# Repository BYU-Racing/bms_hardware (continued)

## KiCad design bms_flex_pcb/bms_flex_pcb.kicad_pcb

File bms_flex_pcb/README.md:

# BMS Flex PCBs (FPCs) V1 Files

This was originally intended to be used as the connection from the current collector plates on the modules to the
BMS Cell Monitor PCB V1.01. (the FSAE rules calls this connection the "Voltage sense leads")

The idea to use the FPCs was scrapped for the 2027 season in late October of 2026 due to team integration timeline constraints. We defaulted back to using the long leads off the current collector plates.
This is still a totally viable and incredibly sleek solution for future years (many other FSAE teams use this and EV companies are beginning to move towards a solution similar to this)

The main intent behind using these was as follows:
- instead of using very long tabs on the current collector plates we can solder these very close to the cell stack,
eliminating a lot of risk while manufacturing (because with the long collector plate tabs we have a risk of shorting those tabs to neighboring cells)
- We can have the thermistors soldered directly to the FPC and thus have a closer and better thermal connection to the cells
- Another ease of manufacturing is that we can just lay this across the cells and then solder it and its done.

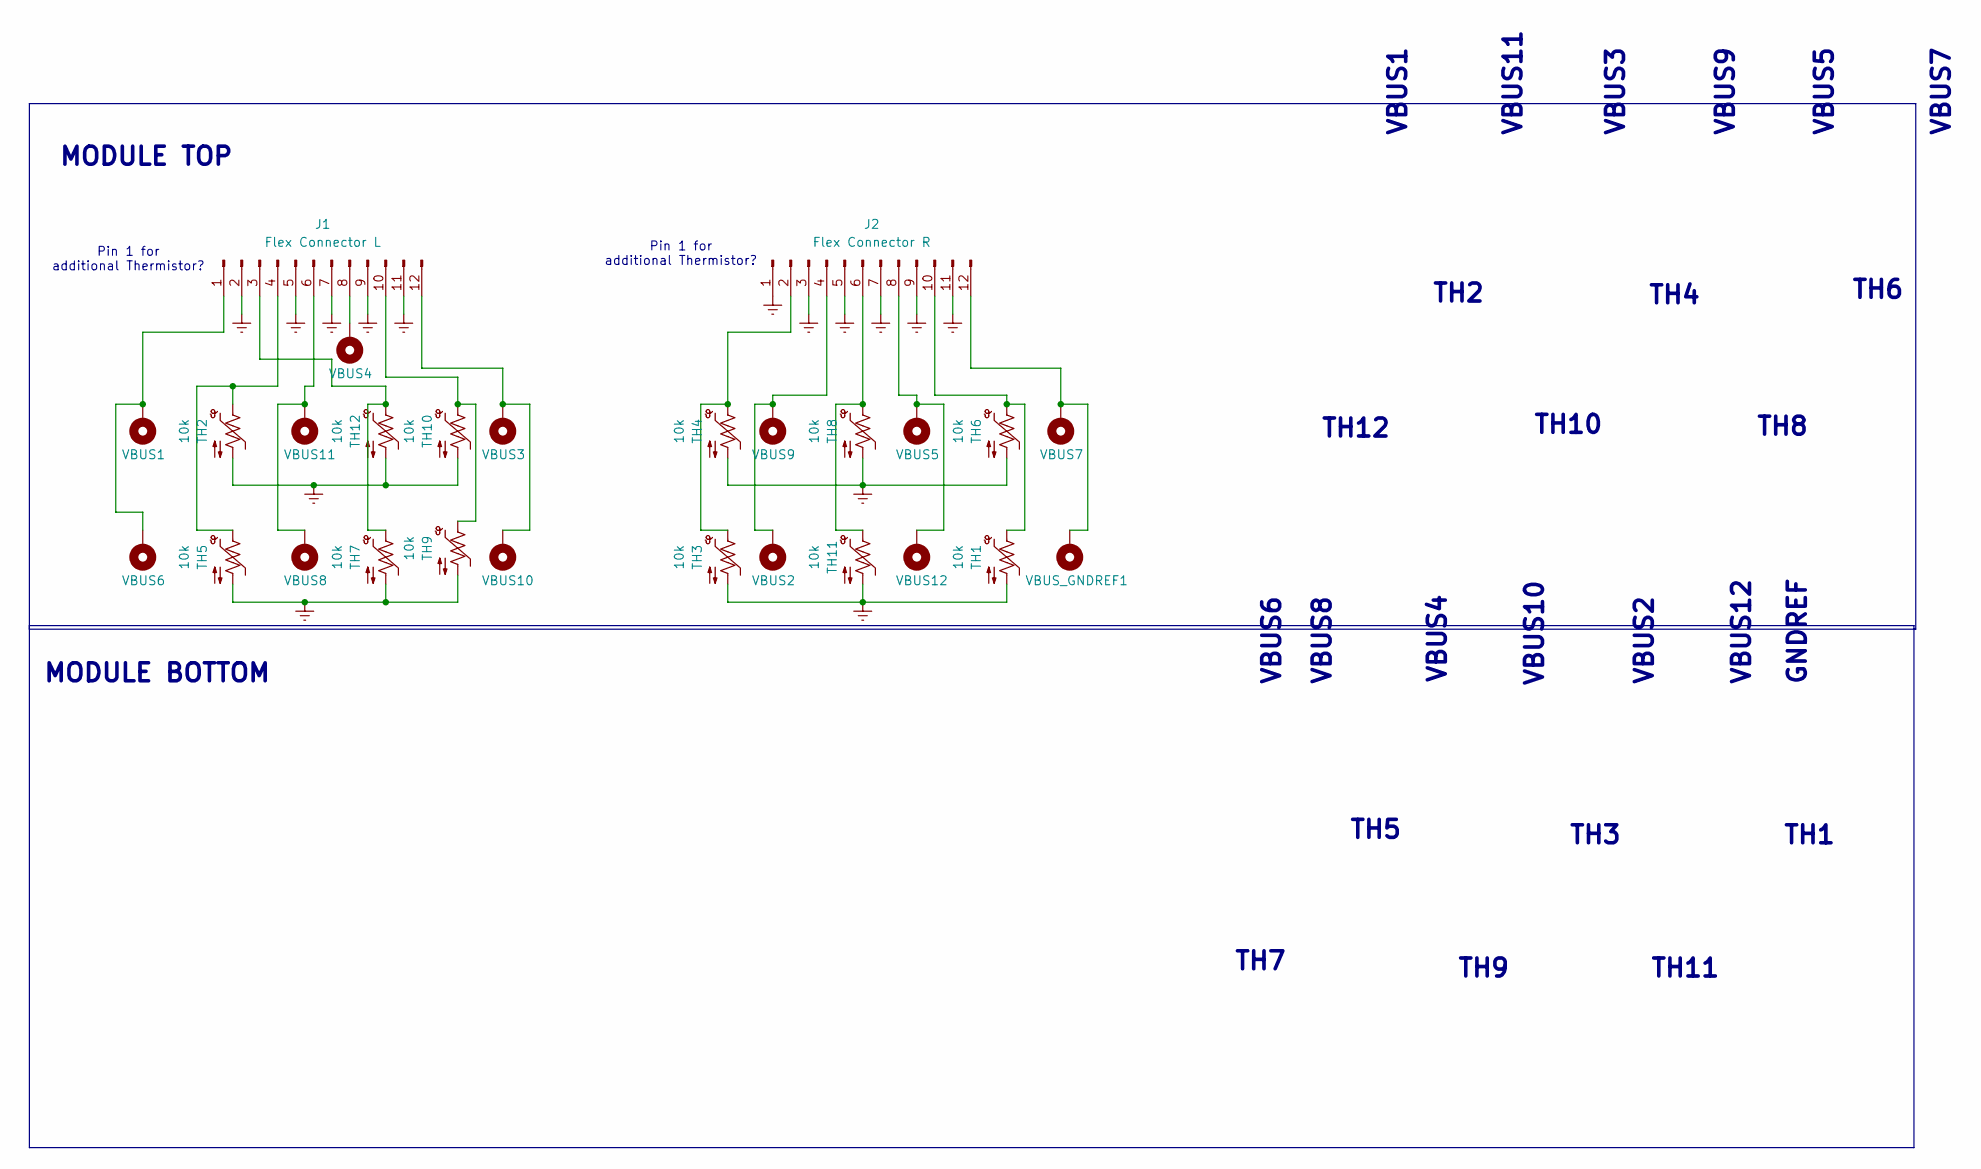
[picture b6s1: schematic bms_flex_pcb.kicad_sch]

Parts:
J1: Flex Connector L; Molex_2190190120_FPC_Board_Connect
J2: Flex Connector R; Molex_2190190120_FPC_Board_Connect
TH1, TH2, TH3, TH4, TH5, TH6, TH7, TH8, TH9, TH10, TH11, TH12: 10k; R_0603_1608Metric_Pad0.98x0.95mm_HandSolder
VBUS1, VBUS2, VBUS3, VBUS4, VBUS5, VBUS6, VBUS7, VBUS8, VBUS9, VBUS10, VBUS11, VBUS12: MountingHole_Pad; 2026_BMS_Voltage_Tap
VBUS_GNDREF1: MountingHole_Pad; 2026_BMS_Voltage_Tap

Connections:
GNDREF: J1.2, J1.5, J1.7, J1.9, J1.11, J2.1, J2.3, J2.5, J2.7, J2.9, J2.11, TH1.2, TH2.2, TH3.2, TH4.2, TH5.2, TH6.2, TH7.2, TH8.2, TH9.2, TH10.2, TH11.2, TH12.2
unnamed: J1.1, VBUS1.1 (1_1), VBUS6.1 (1_1)
unnamed: J1.3, TH7.1, TH12.1
unnamed: J1.4, TH2.1, TH5.1
unnamed: J1.6, VBUS8.1 (1_1), VBUS11.1 (1_1)
unnamed: J1.8, VBUS4.1 (1_1)
unnamed: J1.10, TH9.1, TH10.1
unnamed: J1.12, VBUS3.1 (1_1), VBUS10.1 (1_1)
unnamed: J2.2, TH3.1, TH4.1
unnamed: J2.4, VBUS2.1 (1_1), VBUS9.1 (1_1)
unnamed: J2.6, TH8.1, TH11.1
unnamed: J2.8, VBUS5.1 (1_1), VBUS12.1 (1_1)
unnamed: J2.10, TH1.1, TH6.1
unnamed 13: J2.12, VBUS7.1 (1_1), VBUS_GNDREF1.1; also elsewhere on the board

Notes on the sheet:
GNDREF
TH12
TH7
TH10
MODULE BOTTOM
TH2
VBUS3
VBUS12
VBUS10
TH6
MODULE TOP
Pin 1 for additional Thermistor?
VBUS5
VBUS11
VBUS9
TH8
TH5
TH4
VBUS7
VBUS1
VBUS8
VBUS6
TH3
TH11
VBUS4
TH1
VBUS2
TH9

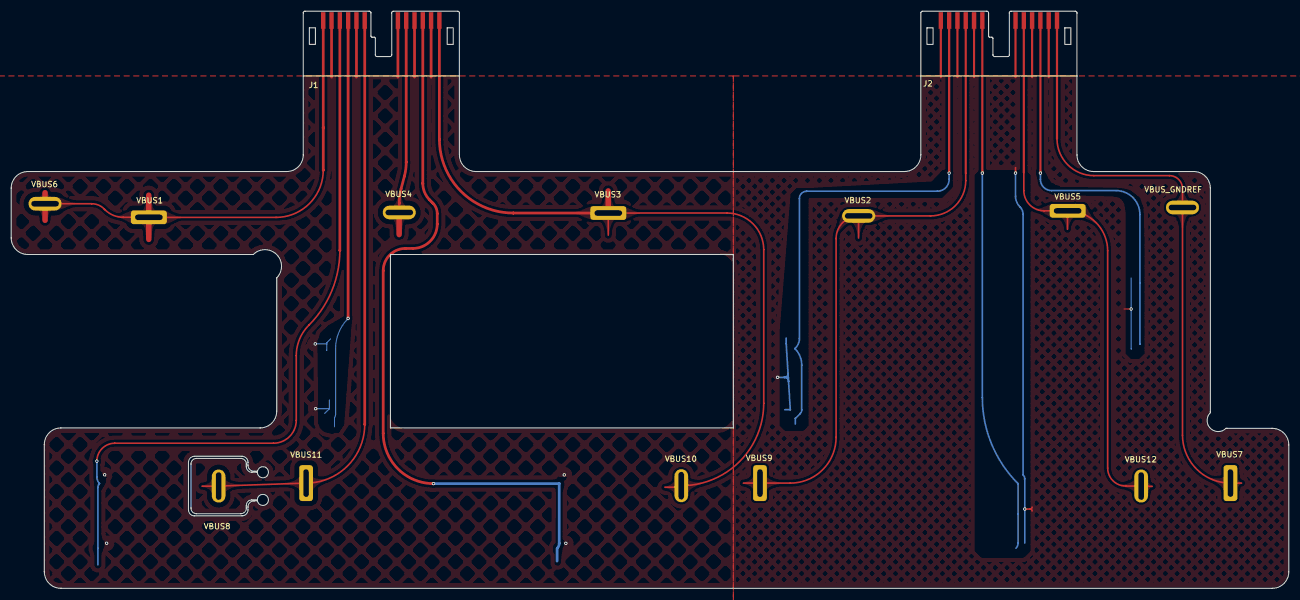
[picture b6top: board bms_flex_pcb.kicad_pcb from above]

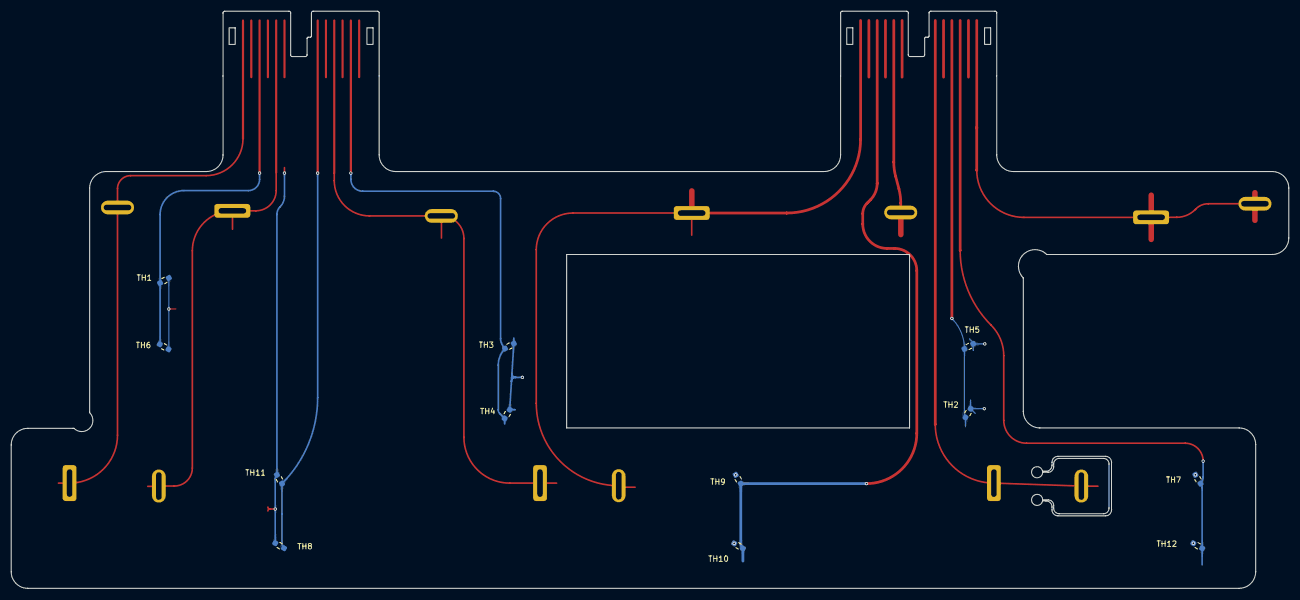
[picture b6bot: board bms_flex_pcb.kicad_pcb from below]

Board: 2 copper layers, 231.0 x 104.3 mm, 27 parts (12 on the bottom side), 14 nets.

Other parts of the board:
VBUS_GNDREF: MountingHole_Pad; 2026_BMS_Voltage_Tap

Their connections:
unnamed 13: VBUS_GNDREF.1 (1_1); also elsewhere on the board

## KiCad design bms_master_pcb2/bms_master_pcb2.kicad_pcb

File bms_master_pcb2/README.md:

## BMS Control Unit V1.01 KiCad Files

These PCB files are for the first version for the BMS Control Unit V1.01 (previously known as the BMS Master V1.01)

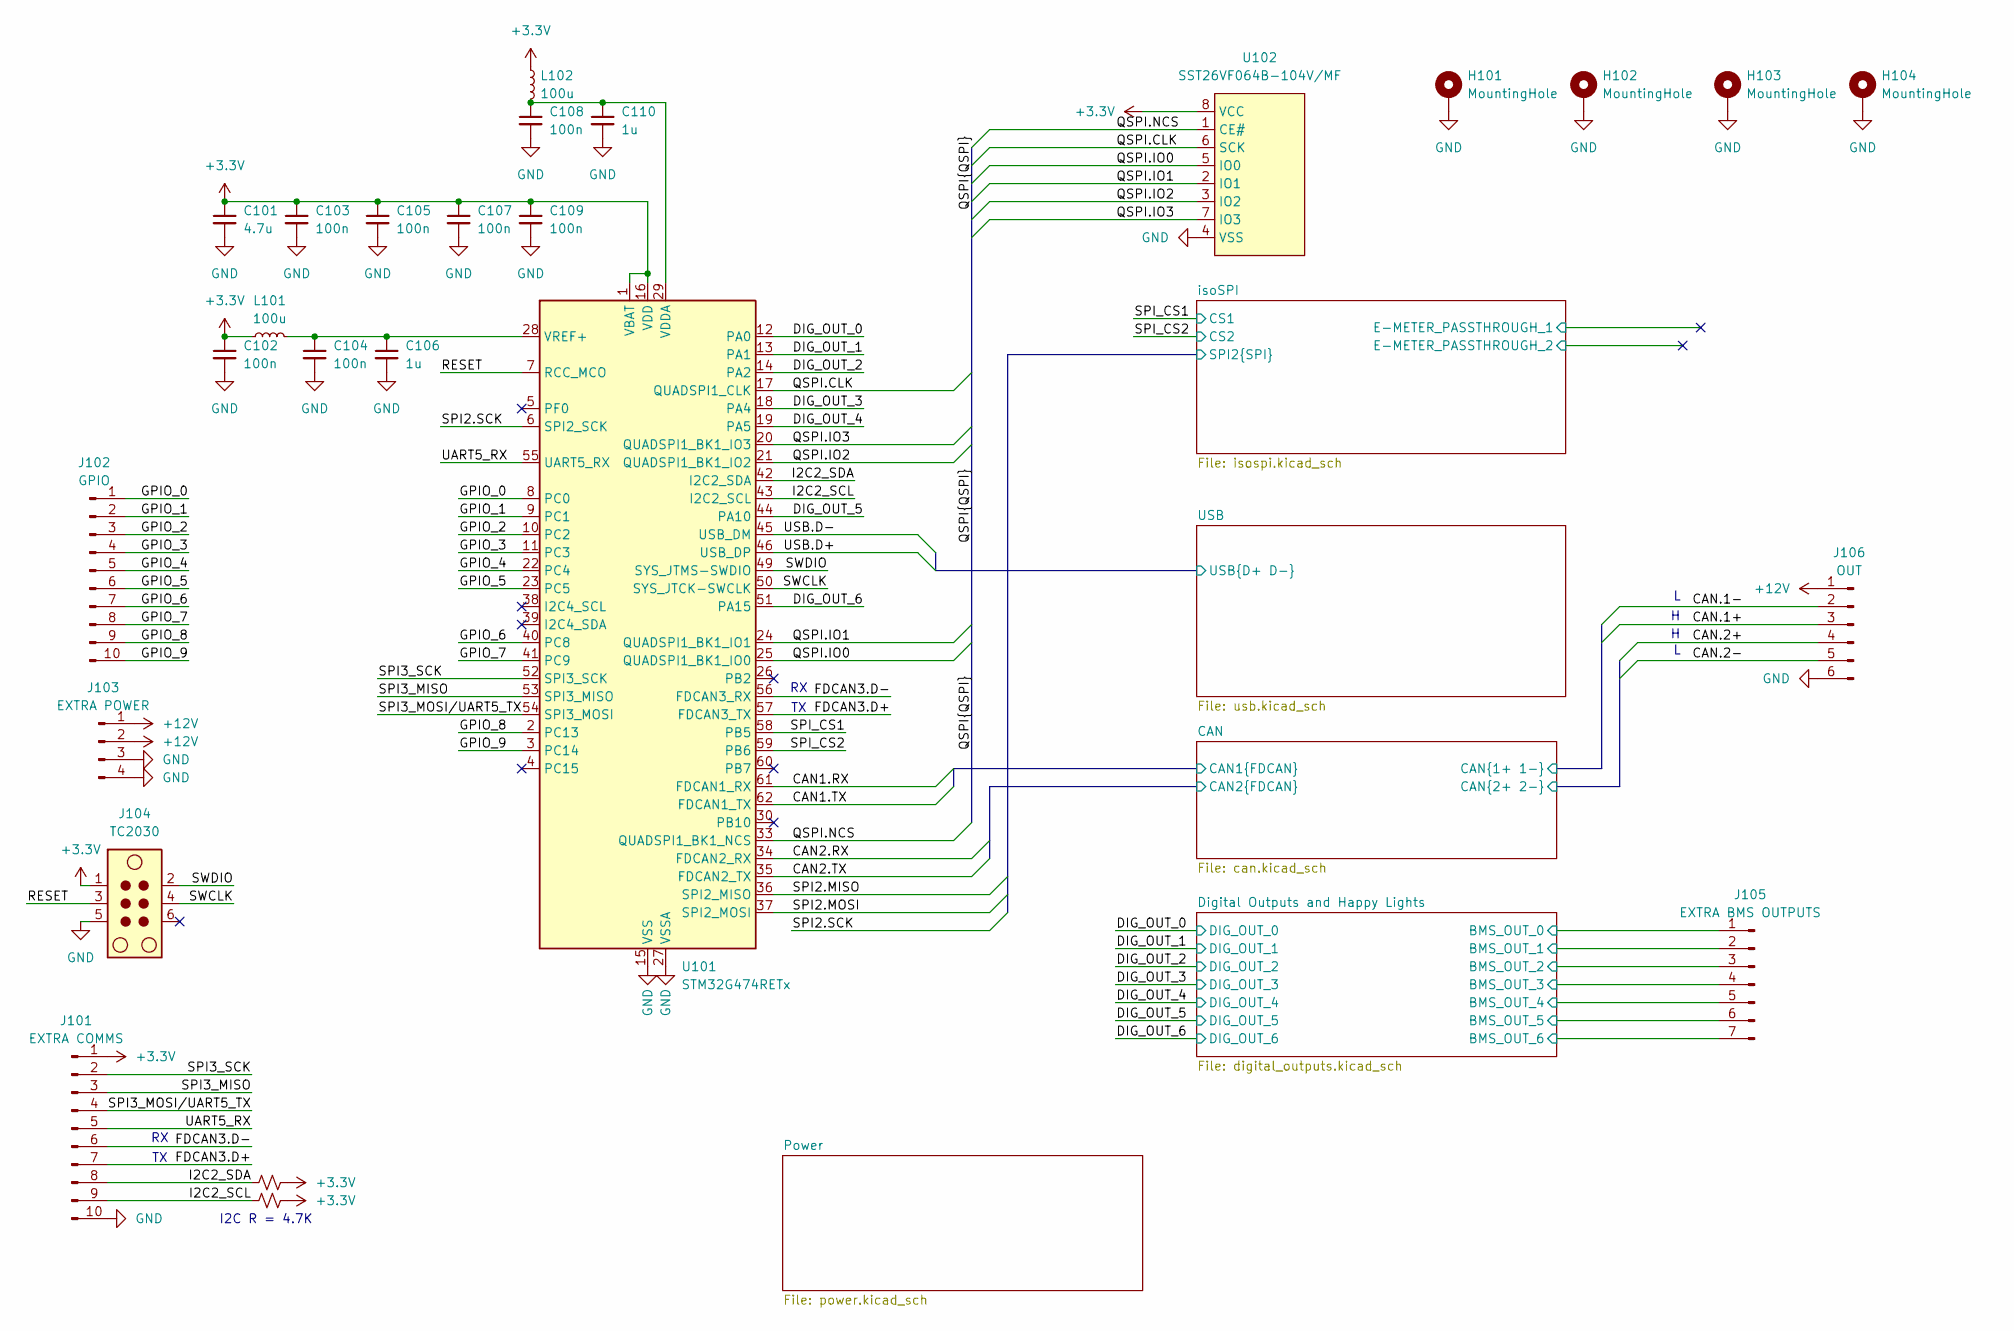
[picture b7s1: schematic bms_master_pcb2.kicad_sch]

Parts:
C101: 4.7u; C_0805_2012Metric_Pad1.18x1.45mm_HandSolder
C102, C103, C104, C105, C107, C108, C109: 100n; C_0603_1608Metric_Pad1.08x0.95mm_HandSolder
C106, C110: 1u; C_0805_2012Metric_Pad1.18x1.45mm_HandSolder
H101, H102, H103, H104: MountingHole; MountingHole_3.2mm_M3_Pad
J101: EXTRA COMMS; PinHeader_1x10_P2.54mm_Vertical
J102: GPIO; PinHeader_1x10_P2.54mm_Vertical
J103: EXTRA POWER; PinHeader_1x04_P2.54mm_Vertical
J104: TC2030; Tag-Connect_TC2030-IDC-NL_2x03_P1.27mm_Vertical
J105: EXTRA BMS OUTPUTS; PinHeader_1x07_P2.54mm_Vertical
J106: OUT; PinHeader_1x06_P2.54mm_Vertical
L101, L102: 100u; WE-HEPC_6030
R101, R102: 4.7K; R_0603_1608Metric_Pad0.98x0.95mm_HandSolder
U101: STM32G474RETx; LQFP-64_10x10mm_P0.5mm
U102: SST26VF064B-104V/MF; WDFN-8-1EP_6x5mm_P1.27mm_EP3.4x4mm

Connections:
+3.3V: C101.1, C102.1, C103.1, C105.1, C107.1, C109.1, J101.1, J104.1, L101.1, L102.1, R101.2, R102.2, U101.1 (VBAT), U101.16 (VDD), U101.32 (VDD), U101.48 (VDD), U101.64 (VDD), U102.8 (VCC); also elsewhere on the board
/CAN/CAN1.RX: U101.61 (FDCAN1_RX); also elsewhere on the board
/CAN/CAN1.TX: U101.62 (FDCAN1_TX); also elsewhere on the board
/CAN/CAN2.RX: U101.34 (FDCAN2_RX); also elsewhere on the board
/CAN/CAN2.TX: U101.35 (FDCAN2_TX); also elsewhere on the board
/CAN/CAN.1+: J106.3; also elsewhere on the board
/CAN/CAN.1-: J106.2; also elsewhere on the board
/CAN/CAN.2+: J106.4; also elsewhere on the board
/CAN/CAN.2-: J106.5; also elsewhere on the board
/DIG_OUT_0: U101.12 (PA0); also elsewhere on the board
/DIG_OUT_1: U101.13 (PA1); also elsewhere on the board
/DIG_OUT_2: U101.14 (PA2); also elsewhere on the board
/DIG_OUT_3: U101.18 (PA4); also elsewhere on the board
/DIG_OUT_4: U101.19 (PA5); also elsewhere on the board
/DIG_OUT_5: U101.44 (PA10); also elsewhere on the board
/DIG_OUT_6: U101.51 (PA15); also elsewhere on the board
/Digital Outputs and Happy Lights/BMS_OUT_0: J105.1; also elsewhere on the board
/Digital Outputs and Happy Lights/BMS_OUT_1: J105.2; also elsewhere on the board
/Digital Outputs and Happy Lights/BMS_OUT_2: J105.3; also elsewhere on the board
/Digital Outputs and Happy Lights/BMS_OUT_3: J105.4; also elsewhere on the board
/Digital Outputs and Happy Lights/BMS_OUT_4: J105.5; also elsewhere on the board
/Digital Outputs and Happy Lights/BMS_OUT_5: J105.6; also elsewhere on the board
/Digital Outputs and Happy Lights/BMS_OUT_6: J105.7; also elsewhere on the board
/FDCAN3.D+: J101.7, U101.57 (FDCAN3_TX)
/FDCAN3.D-: J101.6, U101.56 (FDCAN3_RX)
/GPIO_0: J102.1, U101.8 (PC0)
/GPIO_1: J102.2, U101.9 (PC1)
/GPIO_2: J102.3, U101.10 (PC2)
/GPIO_3: J102.4, U101.11 (PC3)
/GPIO_4: J102.5, U101.22 (PC4)
/GPIO_5: J102.6, U101.23 (PC5)
/GPIO_6: J102.7, U101.40 (PC8)
/GPIO_7: J102.8, U101.41 (PC9)
/GPIO_8: J102.9, U101.2 (PC13)
/GPIO_9: J102.10, U101.3 (PC14)
/I2C2_SCL: J101.9, R102.1, U101.43 (I2C2_SCL)
/I2C2_SDA: J101.8, R101.1, U101.42 (I2C2_SDA)
/QSPI.CLK: U101.17 (QUADSPI1_CLK), U102.6 (SCK)
/QSPI.IO0: U101.25 (QUADSPI1_BK1_IO0), U102.5 (IO0)
/QSPI.IO1: U101.24 (QUADSPI1_BK1_IO1), U102.2 (IO1)
/QSPI.IO2: U101.21 (QUADSPI1_BK1_IO2), U102.3 (IO2)
/QSPI.IO3: U101.20 (QUADSPI1_BK1_IO3), U102.7 (IO3)
/QSPI.NCS: U101.33 (QUADSPI1_BK1_NCS), U102.1 (CE#)
/RESET: J104.3, U101.7 (RCC_MCO)
/SPI3_MISO: J101.3, U101.53 (SPI3_MISO)
/SPI3_MOSI/UART5_TX: J101.4, U101.54 (SPI3_MOSI)
/SPI3_SCK: J101.2, U101.52 (SPI3_SCK)
/SPI_CS1: U101.58 (PB5); also elsewhere on the board
/SPI_CS2: U101.59 (PB6); also elsewhere on the board
/SWCLK: J104.4, U101.50 (SYS_JTCK-SWCLK)
/SWDIO: J104.2, U101.49 (SYS_JTMS-SWDIO)
/UART5_RX: J101.5, U101.55 (UART5_RX)
/USB/USB.D+: U101.46 (USB_DP); also elsewhere on the board
/USB/USB.D-: U101.45 (USB_DM); also elsewhere on the board
/isoSPI/SPI2.MISO: U101.36 (SPI2_MISO); also elsewhere on the board
/isoSPI/SPI2.MOSI: U101.37 (SPI2_MOSI); also elsewhere on the board
/isoSPI/SPI2.SCK: U101.6 (SPI2_SCK); also elsewhere on the board
unnamed: C108.1, C110.1, L102.2, U101.29 (VDDA)
unnamed: C104.1, C106.1, L101.2, U101.28 (VREF+)

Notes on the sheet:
I2C R = 4.7K

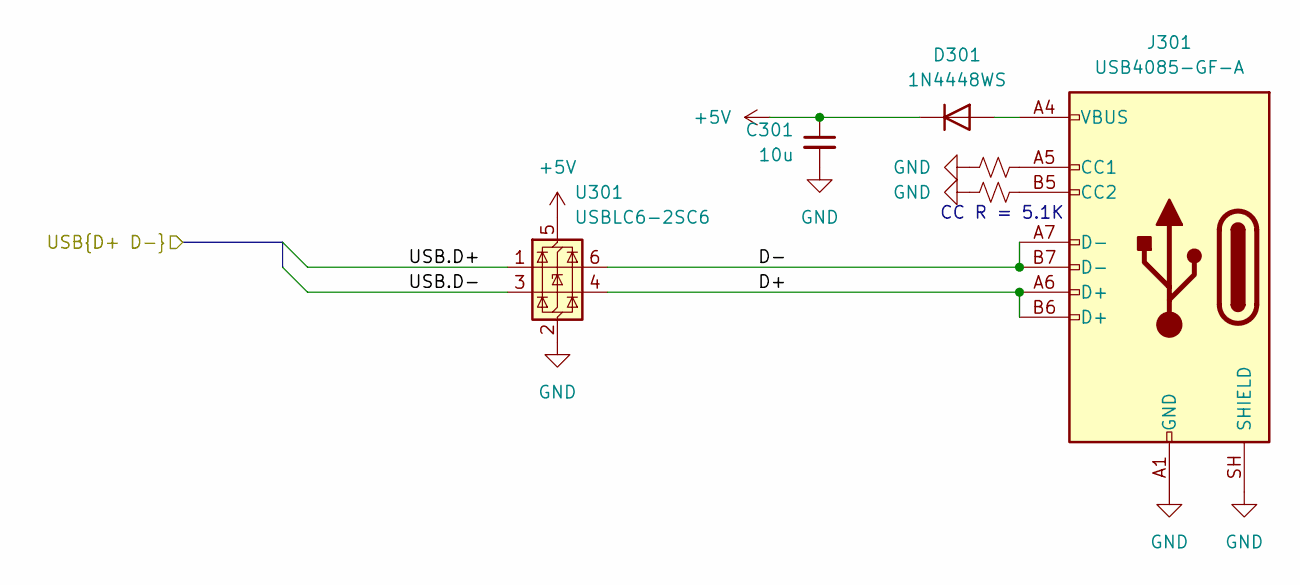
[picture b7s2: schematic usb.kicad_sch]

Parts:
C301: 10u; C_0805_2012Metric_Pad1.18x1.45mm_HandSolder
D301: 1N4448WS; D_SOD-323_HandSoldering
J301: USB4085-GF-A; USB_C_Receptacle_GCT_USB4085
R301, R302: 5.1K; R_0603_1608Metric_Pad0.98x0.95mm_HandSolder
U301: USBLC6-2SC6; SOT-23-6

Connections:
+5V: C301.1, D301.1 (K), U301.5 (VBUS); also elsewhere on the board
/USB/D+: J301.A6 (D+), J301.B6 (D+), U301.4 (I/O2)
/USB/D-: J301.A7 (D-), J301.B7 (D-), U301.6 (I/O1)
/USB/USB.D+: U301.1 (I/O1); also elsewhere on the board
/USB/USB.D-: U301.3 (I/O2); also elsewhere on the board
unnamed: D301.2 (A), J301.A4 (VBUS), J301.A9 (VBUS), J301.B4 (VBUS), J301.B9 (VBUS)
unnamed: J301.A5 (CC1), R301.1
unnamed: J301.B5 (CC2), R302.1

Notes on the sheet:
CC R = 5.1K

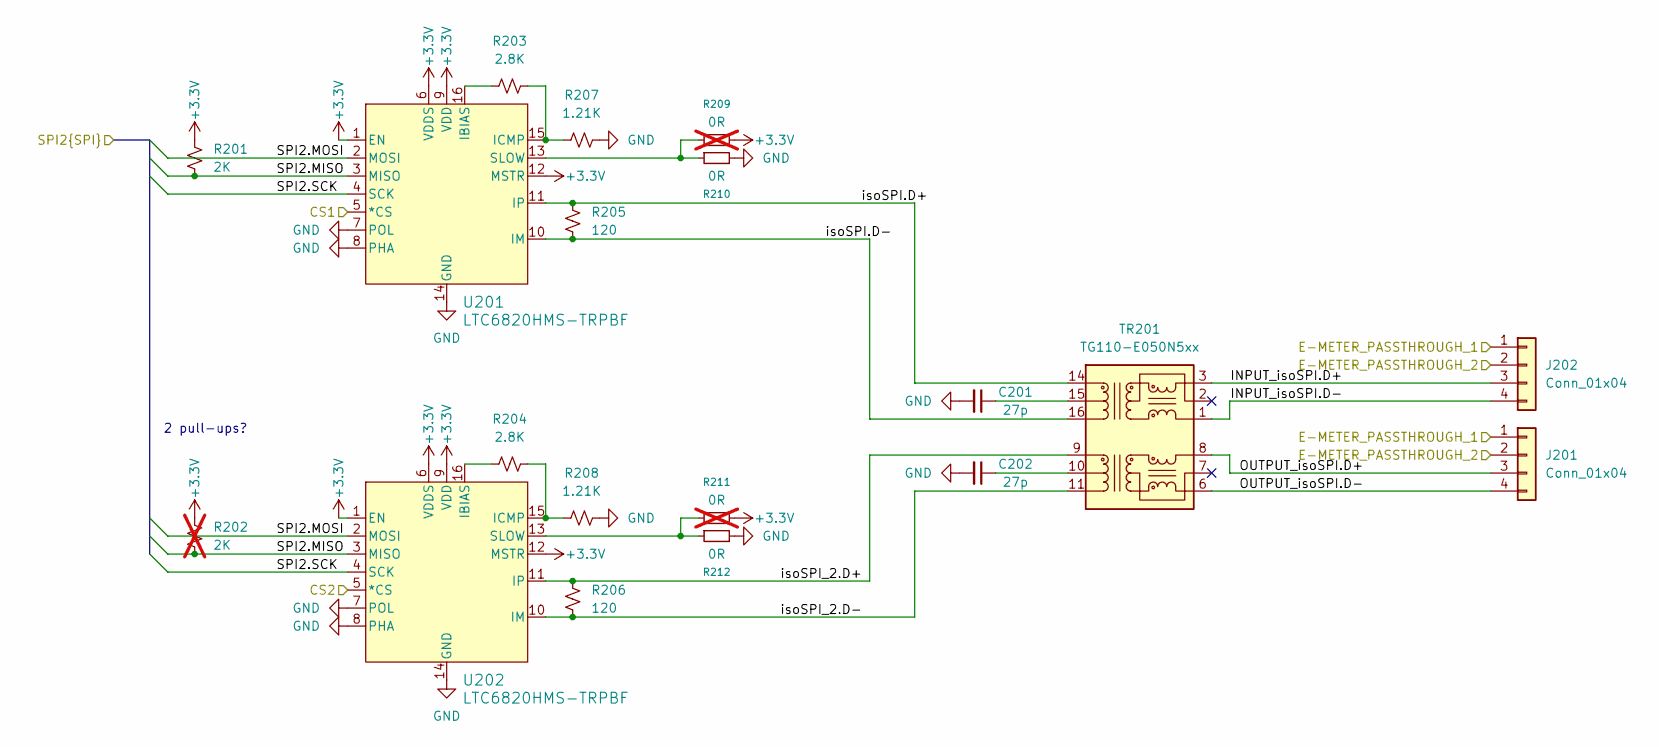
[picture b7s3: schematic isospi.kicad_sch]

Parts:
C201, C202: 27p; C_0603_1608Metric_Pad1.08x0.95mm_HandSolder
J201, J202: Conn_01x04; Molex_Micro-Fit_3.0_43650-0400_1x04_P3.00mm_Horizontal
R201: 2K; R_0603_1608Metric_Pad0.98x0.95mm_HandSolder
R202: 2K; R_0603_1608Metric_Pad0.98x0.95mm_HandSolder; not fitted
R203, R204: 2.8K; R_0603_1608Metric_Pad0.98x0.95mm_HandSolder
R205, R206: 120; R_0603_1608Metric_Pad0.98x0.95mm_HandSolder
R207, R208: 1.21K; R_0603_1608Metric_Pad0.98x0.95mm_HandSolder
R209, R211: 0R; R_0603_1608Metric_Pad0.98x0.95mm_HandSolder; not fitted
R210, R212: 0R; R_0603_1608Metric_Pad0.98x0.95mm_HandSolder
TR201: TG110-E050N5xx; Transformer_Ethernet_Halo_N5_SO-16_7.11x12.7mm
U201, U202: LTC6820HMS-TRPBF; MS_05-08-1669_ADI

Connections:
+3.3V: R201.2, R202.2, R209.2, R211.2, U201.1 (EN), U201.6 (VDDS), U201.9 (VDD), U201.12 (MSTR), U202.1 (EN), U202.6 (VDDS), U202.9 (VDD), U202.12 (MSTR); also elsewhere on the board
/SPI_CS1: U201.5 (*CS); also elsewhere on the board
/SPI_CS2: U202.5 (*CS); also elsewhere on the board
/isoSPI/E-METER_PASSTHROUGH_1: J201.1, J202.1
/isoSPI/E-METER_PASSTHROUGH_2: J201.2, J202.2
/isoSPI/INPUT_isoSPI.D+: J202.3, TR201.3 (TX-)
/isoSPI/INPUT_isoSPI.D-: J202.4, TR201.1
/isoSPI/OUTPUT_isoSPI.D+: J201.3, TR201.8 (RX-)
/isoSPI/OUTPUT_isoSPI.D-: J201.4, TR201.6 (RX+)
/isoSPI/SPI2.MISO: R201.1, R202.1, U201.3 (MISO), U202.3 (MISO); also elsewhere on the board
/isoSPI/SPI2.MOSI: U201.2 (MOSI), U202.2 (MOSI); also elsewhere on the board
/isoSPI/SPI2.SCK: U201.4 (SCK), U202.4 (SCK); also elsewhere on the board
/isoSPI/isoSPI.D+: R205.2, TR201.14 (TD-), U201.11 (IP)
/isoSPI/isoSPI.D-: R205.1, TR201.16 (TD+), U201.10 (IM)
/isoSPI/isoSPI_2.D+: R206.2, TR201.9 (RD-), U202.11 (IP)
/isoSPI/isoSPI_2.D-: R206.1, TR201.11 (RD+), U202.10 (IM)
unnamed: C202.1, TR201.10 (C_RD)
unnamed: C201.1, TR201.15 (C_TD)
unnamed: R203.1, U201.16 (IBIAS)
unnamed: R203.2, R207.1, U201.15 (ICMP)
unnamed: R209.1, R210.1, U201.13 (SLOW)
unnamed: R204.1, U202.16 (IBIAS)
unnamed: R204.2, R208.1, U202.15 (ICMP)
unnamed: R211.1, R212.1, U202.13 (SLOW)

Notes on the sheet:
2 pull-ups?

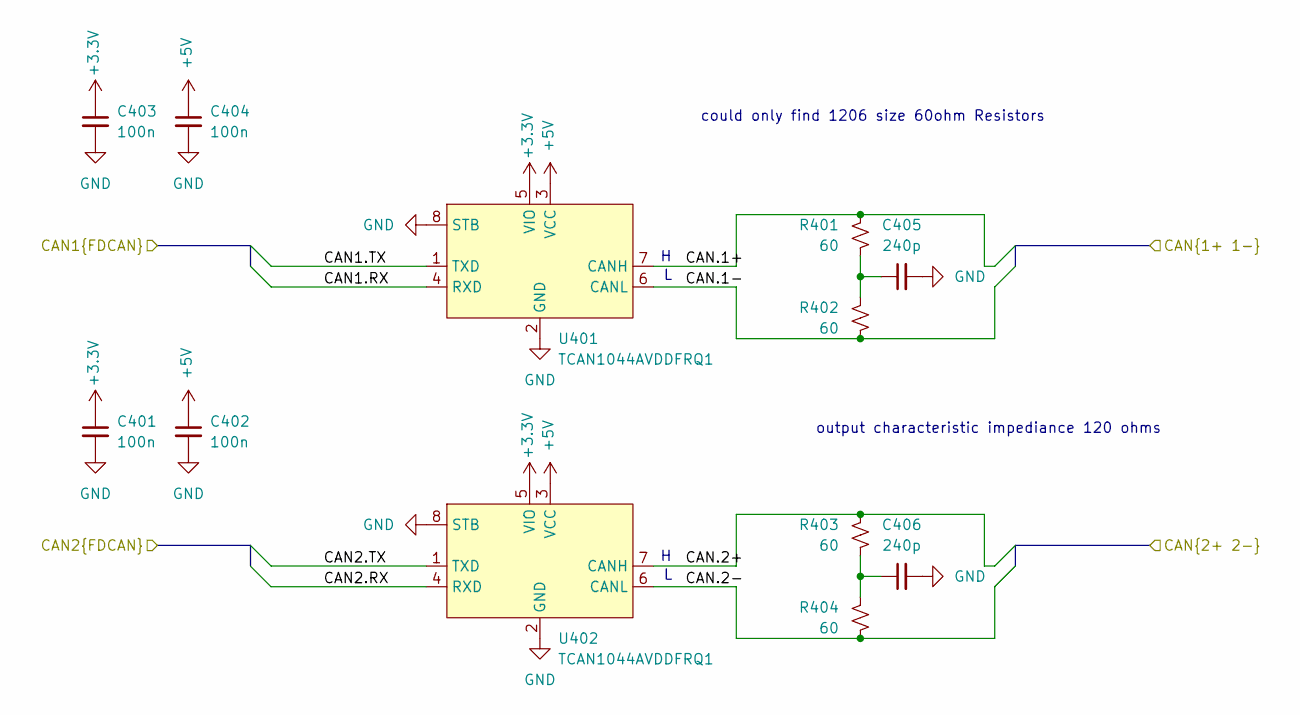
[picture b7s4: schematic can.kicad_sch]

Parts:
C401, C402, C403, C404: 100n; C_0603_1608Metric_Pad1.08x0.95mm_HandSolder
C405, C406: 240p; C_0603_1608Metric_Pad1.08x0.95mm_HandSolder
R401, R402, R403, R404: 60; R_1206_3216Metric_Pad1.30x1.75mm_HandSolder
U401, U402: TCAN1044AVDDFRQ1; TSOT-23-8_HandSoldering

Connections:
+3.3V: C401.1, C403.1, U401.5 (VIO), U402.5 (VIO); also elsewhere on the board
+5V: C402.1, C404.1, U401.3 (VCC), U402.3 (VCC); also elsewhere on the board
/CAN/CAN1.RX: U401.4 (RXD); also elsewhere on the board
/CAN/CAN1.TX: U401.1 (TXD); also elsewhere on the board
/CAN/CAN2.RX: U402.4 (RXD); also elsewhere on the board
/CAN/CAN2.TX: U402.1 (TXD); also elsewhere on the board
/CAN/CAN.1+: R401.1, U401.7 (CANH); also elsewhere on the board
/CAN/CAN.1-: R402.2, U401.6 (CANL); also elsewhere on the board
/CAN/CAN.2+: R403.1, U402.7 (CANH); also elsewhere on the board
/CAN/CAN.2-: R404.2, U402.6 (CANL); also elsewhere on the board
unnamed: C405.1, R401.2, R402.1
unnamed: C406.1, R403.2, R404.1

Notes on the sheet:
output characteristic impediance 120 ohms
could only find 1206 size 60ohm Resistors

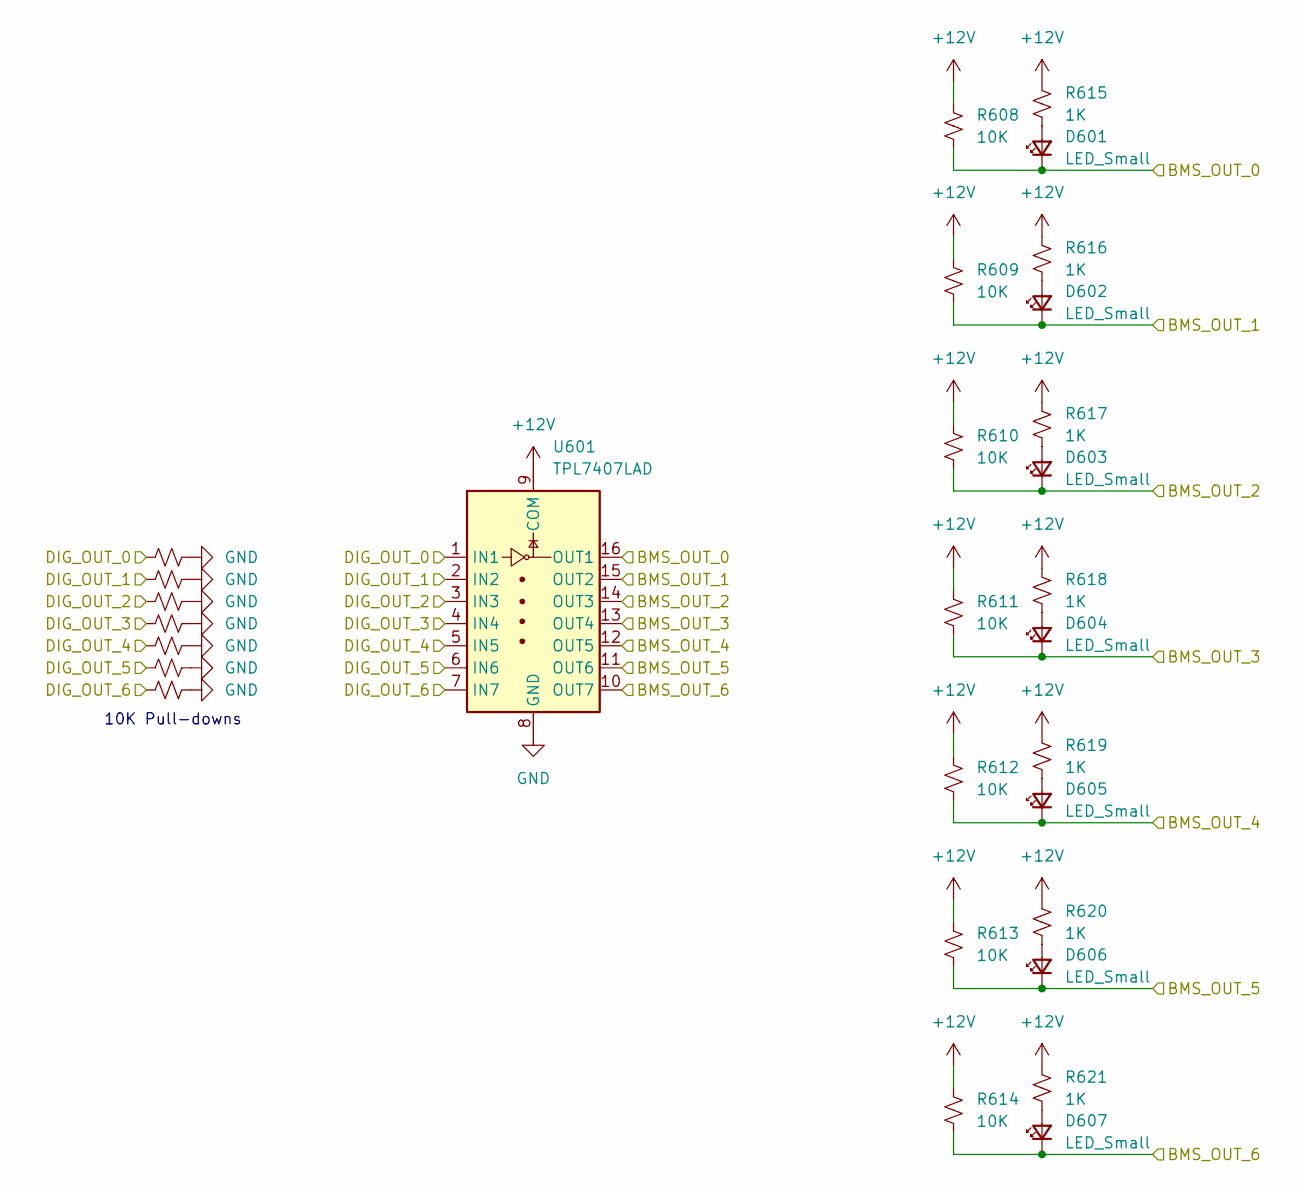
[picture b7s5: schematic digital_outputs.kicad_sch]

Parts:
D601, D602, D603, D604, D605, D606, D607: LED_Small; LED_0603_1608Metric_Pad1.05x0.95mm_HandSolder
R601, R602, R603, R604, R605, R606, R607, R608, R609, R610, R611, R612, R613, R614: 10K; R_0603_1608Metric_Pad0.98x0.95mm_HandSolder
R615, R616, R617, R618, R619, R620, R621: 1K; R_0603_1608Metric_Pad0.98x0.95mm_HandSolder
U601: TPL7407LAD; SOIC-16_3.9x9.9mm_P1.27mm

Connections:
/DIG_OUT_0: R601.1, U601.1 (IN1); also elsewhere on the board
/DIG_OUT_1: R602.1, U601.2 (IN2); also elsewhere on the board
/DIG_OUT_2: R603.1, U601.3 (IN3); also elsewhere on the board
/DIG_OUT_3: R604.1, U601.4 (IN4); also elsewhere on the board
/DIG_OUT_4: R605.1, U601.5 (IN5); also elsewhere on the board
/DIG_OUT_5: R606.1, U601.6 (IN6); also elsewhere on the board
/DIG_OUT_6: R607.1, U601.7 (IN7); also elsewhere on the board
/Digital Outputs and Happy Lights/BMS_OUT_0: D601.1 (K), R608.2, U601.16 (OUT1); also elsewhere on the board
/Digital Outputs and Happy Lights/BMS_OUT_1: D602.1 (K), R609.2, U601.15 (OUT2); also elsewhere on the board
/Digital Outputs and Happy Lights/BMS_OUT_2: D603.1 (K), R610.2, U601.14 (OUT3); also elsewhere on the board
/Digital Outputs and Happy Lights/BMS_OUT_3: D604.1 (K), R611.2, U601.13 (OUT4); also elsewhere on the board
/Digital Outputs and Happy Lights/BMS_OUT_4: D605.1 (K), R612.2, U601.12 (OUT5); also elsewhere on the board
/Digital Outputs and Happy Lights/BMS_OUT_5: D606.1 (K), R613.2, U601.11 (OUT6); also elsewhere on the board
/Digital Outputs and Happy Lights/BMS_OUT_6: D607.1 (K), R614.2, U601.10 (OUT7); also elsewhere on the board
unnamed: D601.2 (A), R615.2
unnamed: D602.2 (A), R616.2
unnamed: D603.2 (A), R617.2
unnamed: D604.2 (A), R618.2
unnamed: D605.2 (A), R619.2
unnamed: D606.2 (A), R620.2
unnamed: D607.2 (A), R621.2

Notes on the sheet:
10K Pull-downs

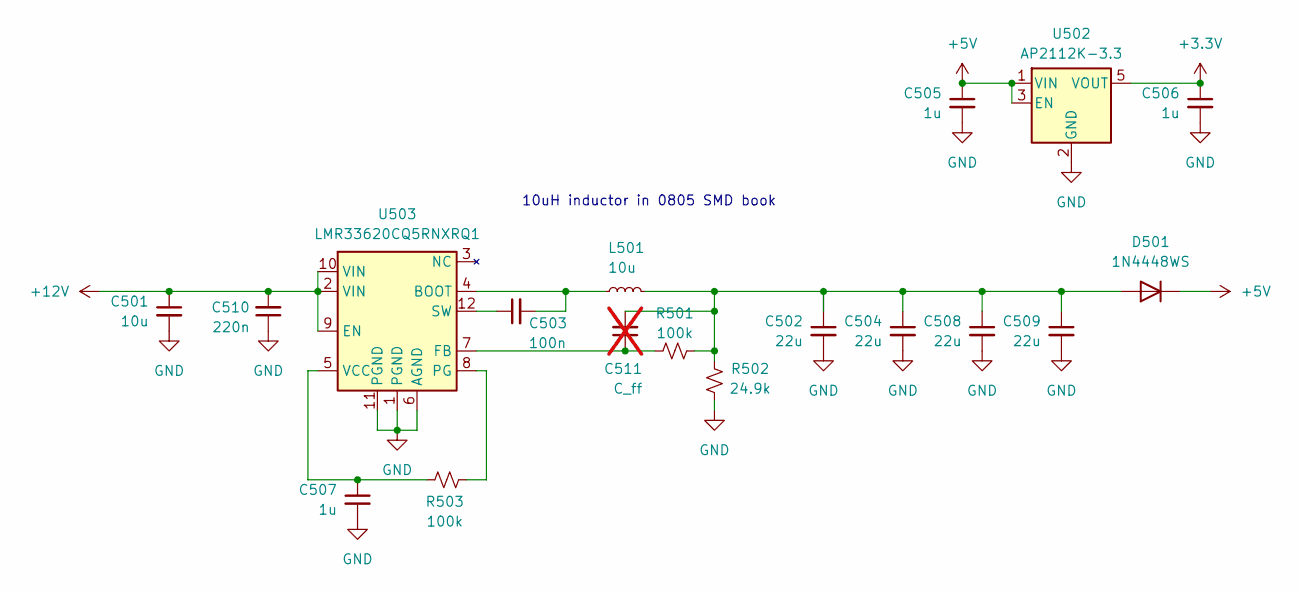
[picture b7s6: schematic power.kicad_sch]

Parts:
C501: 10u; C_0805_2012Metric_Pad1.18x1.45mm_HandSolder
C502, C504, C508, C509: 22u; C_0805_2012Metric_Pad1.18x1.45mm_HandSolder
C503: 100n; C_0603_1608Metric_Pad1.08x0.95mm_HandSolder
C505, C506, C507: 1u; C_0805_2012Metric_Pad1.18x1.45mm_HandSolder
C510: 220n; C_0603_1608Metric_Pad1.08x0.95mm_HandSolder
C511: C_ff; C_0603_1608Metric_Pad1.08x0.95mm_HandSolder; not fitted
D501: 1N4448WS; D_SOD-323_HandSoldering
L501: 10u; L_0805_2012Metric_Pad1.05x1.20mm_HandSolder
R501, R503: 100k; R_0603_1608Metric_Pad0.98x0.95mm_HandSolder
R502: 24.9k; R_0603_1608Metric_Pad0.98x0.95mm_HandSolder
U502: AP2112K-3.3; SOT-23-5
U503: LMR33620CQ5RNXRQ1; RNX0012B

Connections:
+3.3V: C506.1, U502.5 (VOUT); also elsewhere on the board
+5V: C505.1, D501.1 (K), U502.1 (VIN), U502.3 (EN); also elsewhere on the board
unnamed: C502.1, C504.1, C508.1, C509.1, C511.2, D501.2 (A), L501.2, R501.2, R502.1
unnamed: C503.2, L501.1, U503.4 (BOOT)
unnamed: C511.1, R501.1, U503.7 (FB)
unnamed: R503.2, U503.8 (PG)
unnamed: C503.1, U503.12 (SW)
unnamed: C507.1, R503.1, U503.5 (VCC)

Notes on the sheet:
10uH inductor in 0805 SMD book

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
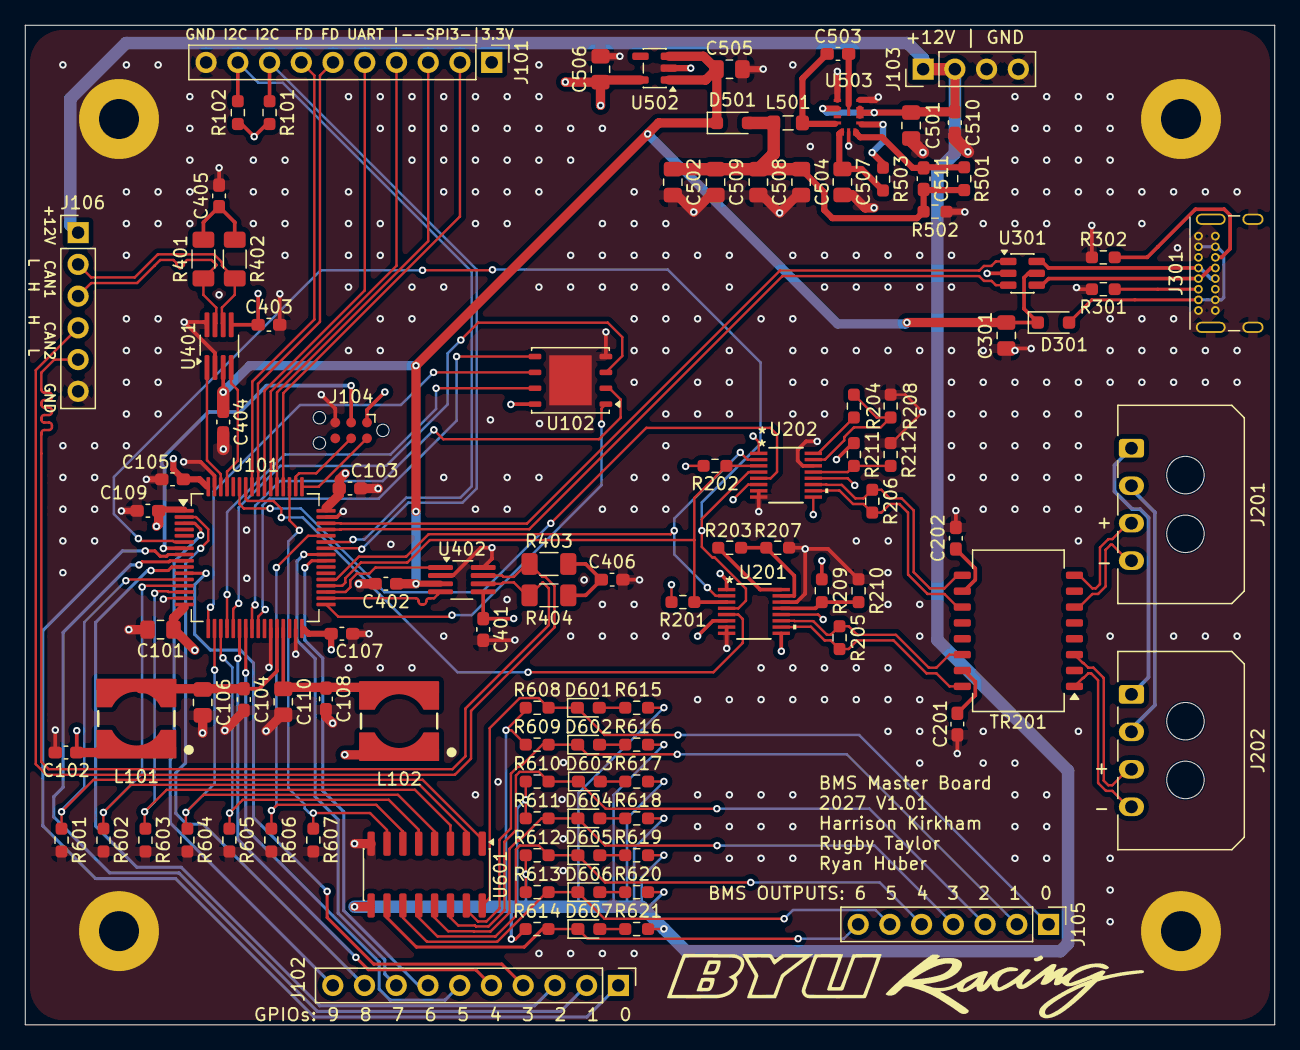
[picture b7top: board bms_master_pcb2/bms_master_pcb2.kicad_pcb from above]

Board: 4 copper layers, 100.0 x 80.0 mm, 110 parts (0 on the bottom side), 100 nets.
